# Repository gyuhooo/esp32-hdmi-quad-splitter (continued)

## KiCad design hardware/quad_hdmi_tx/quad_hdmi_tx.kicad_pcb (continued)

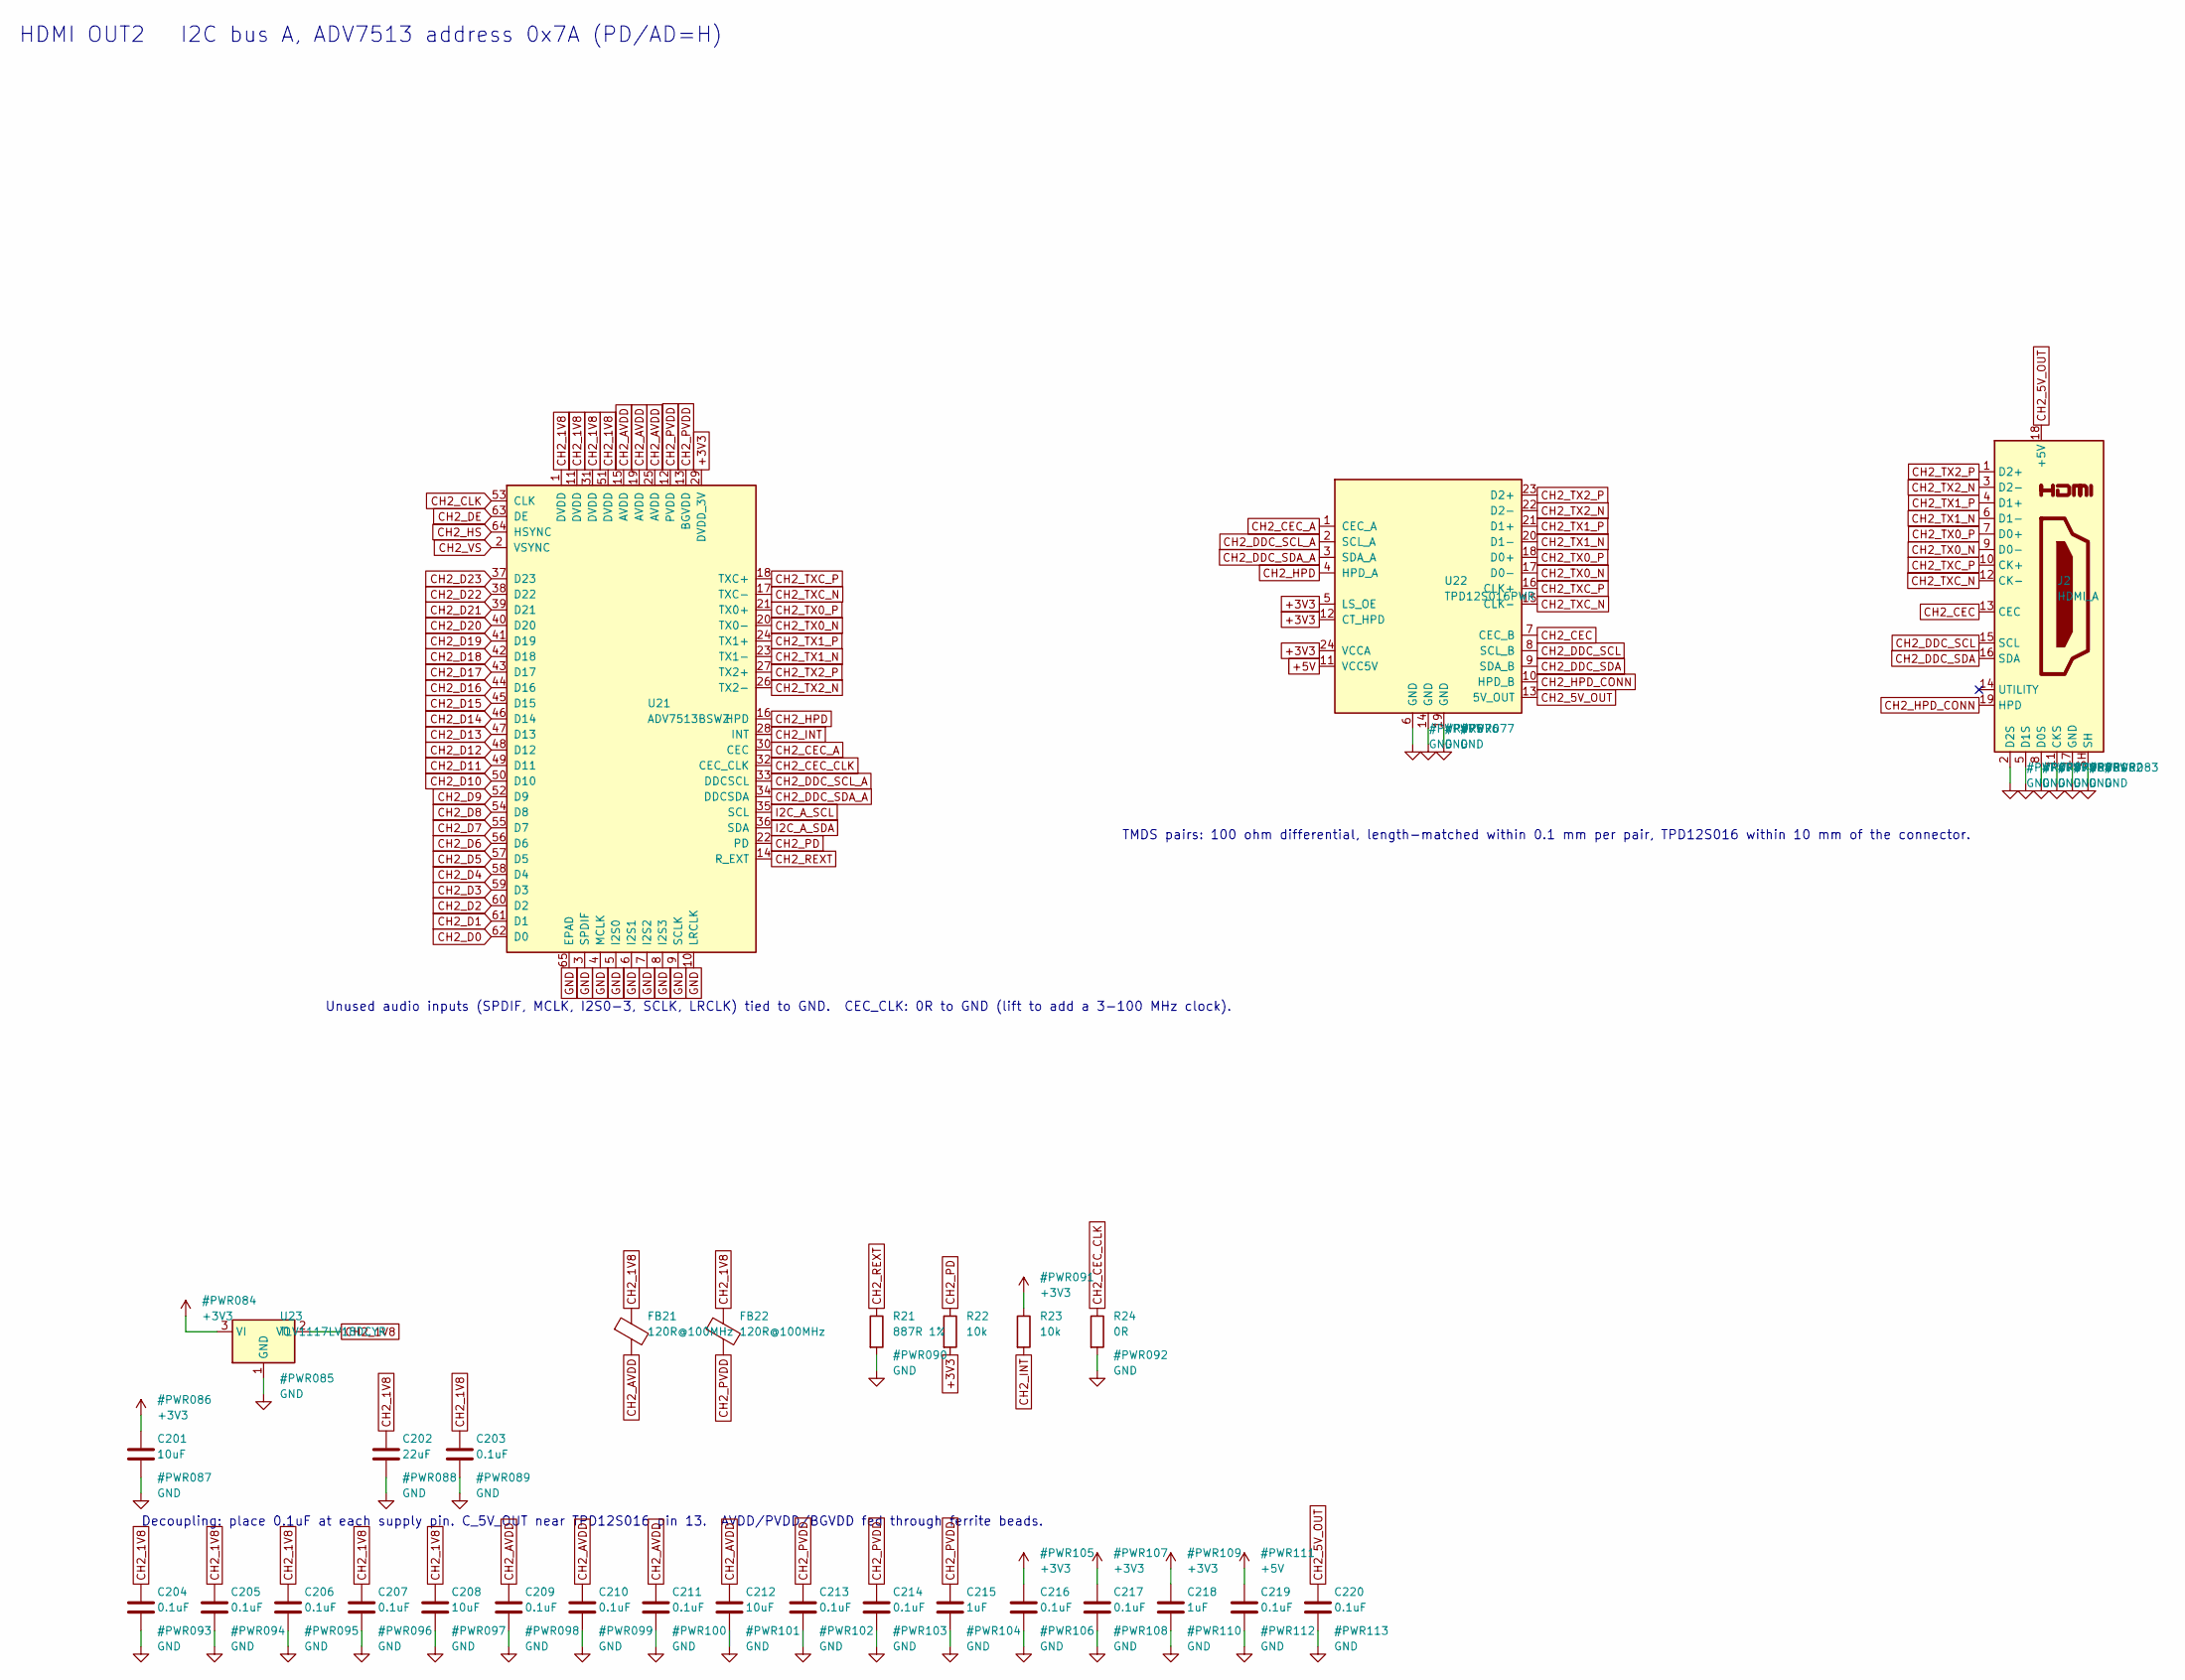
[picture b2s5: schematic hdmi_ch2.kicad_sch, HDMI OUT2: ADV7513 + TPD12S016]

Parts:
C201, C208, C212: 10uF; C_0603_1608Metric; MPN GRM188R60J106ME47D
C202: 22uF; C_0805_2012Metric; MPN GRM21BR60J226ME39L
C203, C204, C205, C206, C207, C209, C210, C211, C213, C214, C216, C217, C219, C220: 0.1uF; C_0402_1005Metric; MPN GRM155R71C104KA88D
C215, C218: 1uF; C_0603_1608Metric; MPN GRM188R61A105KA61D
FB21, FB22: 120R@100MHz; L_0603_1608Metric; MPN BLM18PG121SN1D
J2: HDMI_A; HDMI_A_Molex_208658-1001_Horizontal; MPN 208658-1001
R21: 887R 1%; R_0402_1005Metric; MPN RC0402FR-07887RL
R22, R23: 10k; R_0402_1005Metric; MPN RC0402FR-0710KL
R24: 0R; R_0402_1005Metric; MPN RC0402FR-070RL
U21: ADV7513BSWZ; LQFP-64-1EP_10x10mm_P0.5mm_EP5x5mm; MPN ADV7513BSWZ
U22: TPD12S016PWR; TSSOP-24_4.4x7.8mm_P0.65mm; MPN TPD12S016PWR
U23: TLV1117LV18DCYR; SOT-223-3_TabPin2; MPN TLV1117LV18DCYR

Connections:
+3V3: C201.1, C216.1, C217.1, C218.1, R22.2, R23.1, U21.29 (DVDD_3V), U22.5 (LS_OE), U22.12 (CT_HPD), U22.24 (VCCA), U23.3 (VI); also elsewhere on the board
+5V: C219.1, U22.11 (VCC5V); also elsewhere on the board
CH2_1V8: C202.1, C203.1, C204.1, C205.1, C206.1, C207.1, C208.1, FB21.1, FB22.1, U21.1 (DVDD), U21.11 (DVDD), U21.31 (DVDD), U21.51 (DVDD), U23.2 (VO)
CH2_5V_OUT: C220.1, J2.18 (+5V), U22.13 (5V_OUT)
CH2_AVDD: C209.1, C210.1, C211.1, C212.1, FB21.2, U21.15 (AVDD), U21.19 (AVDD), U21.25 (AVDD)
CH2_CEC: J2.13 (CEC), U22.7 (CEC_B)
CH2_CEC_A: U21.30 (CEC), U22.1 (CEC_A)
CH2_CEC_CLK: R24.1, U21.32 (CEC_CLK)
CH2_CLK: U21.53 (CLK); also elsewhere on the board
CH2_D0: U21.62 (D0); also elsewhere on the board
CH2_D1: U21.61 (D1); also elsewhere on the board
CH2_D2: U21.60 (D2); also elsewhere on the board
CH2_D3: U21.59 (D3); also elsewhere on the board
CH2_D4: U21.58 (D4); also elsewhere on the board
CH2_D5: U21.57 (D5); also elsewhere on the board
CH2_D6: U21.56 (D6); also elsewhere on the board
CH2_D7: U21.55 (D7); also elsewhere on the board
CH2_D8: U21.54 (D8); also elsewhere on the board
CH2_D9: U21.52 (D9); also elsewhere on the board
CH2_D10: U21.50 (D10); also elsewhere on the board
CH2_D11: U21.49 (D11); also elsewhere on the board
CH2_D12: U21.48 (D12); also elsewhere on the board
CH2_D13: U21.47 (D13); also elsewhere on the board
CH2_D14: U21.46 (D14); also elsewhere on the board
CH2_D15: U21.45 (D15); also elsewhere on the board
CH2_D16: U21.44 (D16); also elsewhere on the board
CH2_D17: U21.43 (D17); also elsewhere on the board
CH2_D18: U21.42 (D18); also elsewhere on the board
CH2_D19: U21.41 (D19); also elsewhere on the board
CH2_D20: U21.40 (D20); also elsewhere on the board
CH2_D21: U21.39 (D21); also elsewhere on the board
CH2_D22: U21.38 (D22); also elsewhere on the board
CH2_D23: U21.37 (D23); also elsewhere on the board
CH2_DDC_SCL: J2.15 (SCL), U22.8 (SCL_B)
CH2_DDC_SCL_A: U21.33 (DDCSCL), U22.2 (SCL_A)
CH2_DDC_SDA: J2.16 (SDA), U22.9 (SDA_B)
CH2_DDC_SDA_A: U21.34 (DDCSDA), U22.3 (SDA_A)
CH2_DE: U21.63 (DE); also elsewhere on the board
CH2_HPD: U21.16 (HPD), U22.4 (HPD_A); also elsewhere on the board
CH2_HPD_CONN: J2.19 (HPD), U22.10 (HPD_B)
CH2_HS: U21.64 (HSYNC); also elsewhere on the board
CH2_INT: R23.2, U21.28 (INT); also elsewhere on the board
CH2_PD: R22.1, U21.22 (PD)
CH2_PVDD: C213.1, C214.1, C215.1, FB22.2, U21.12 (PVDD), U21.13 (BGVDD)
CH2_REXT: R21.1, U21.14 (R_EXT)
CH2_TX0_N: J2.9 (D0-), U21.20 (TX0-), U22.17 (D0-)
CH2_TX0_P: J2.7 (D0+), U21.21 (TX0+), U22.18 (D0+)
CH2_TX1_N: J2.6 (D1-), U21.23 (TX1-), U22.20 (D1-)
CH2_TX1_P: J2.4 (D1+), U21.24 (TX1+), U22.21 (D1+)
CH2_TX2_N: J2.3 (D2-), U21.26 (TX2-), U22.22 (D2-)
CH2_TX2_P: J2.1 (D2+), U21.27 (TX2+), U22.23 (D2+)
CH2_TXC_N: J2.12 (CK-), U21.17 (TXC-), U22.15 (CLK-)
CH2_TXC_P: J2.10 (CK+), U21.18 (TXC+), U22.16 (CLK+)
CH2_VS: U21.2 (VSYNC); also elsewhere on the board
GND: C201.2, C202.2, C203.2, C204.2, C205.2, C206.2, C207.2, C208.2, C209.2, C210.2, C211.2, C212.2, C213.2, C214.2, C215.2, C216.2, C217.2, C218.2, C219.2, C220.2, J2.2 (D2S), J2.5 (D1S), J2.8 (D0S), J2.11 (CKS), J2.17 (GND), J2.SH, R21.2, R24.2, U21.3 (SPDIF), U21.4 (MCLK), U21.5 (I2S0), U21.6 (I2S1), U21.7 (I2S2), U21.8 (I2S3), U21.9 (SCLK), U21.10 (LRCLK), U21.65 (EPAD), U22.6 (GND), U22.14 (GND), U22.19 (GND), U23.1 (GND); also elsewhere on the board
I2C_A_SCL: U21.35 (SCL); also elsewhere on the board
I2C_A_SDA: U21.36 (SDA); also elsewhere on the board

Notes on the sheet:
HDMI OUT2 I2C bus A, ADV7513 address 0x7A (PD/AD=H)
Unused audio inputs (SPDIF, MCLK, I2S0-3, SCLK, LRCLK) tied to GND. CEC_CLK: 0R to GND (lift to add a 3-100 MHz clock).
Decoupling: place 0.1uF at each supply pin. C_5V_OUT near TPD12S016 pin 13. AVDD/PVDD/BGVDD fed through ferrite beads.
TMDS pairs: 100 ohm differential, length-matched within 0.1 mm per pair, TPD12S016 within 10 mm of the connector.

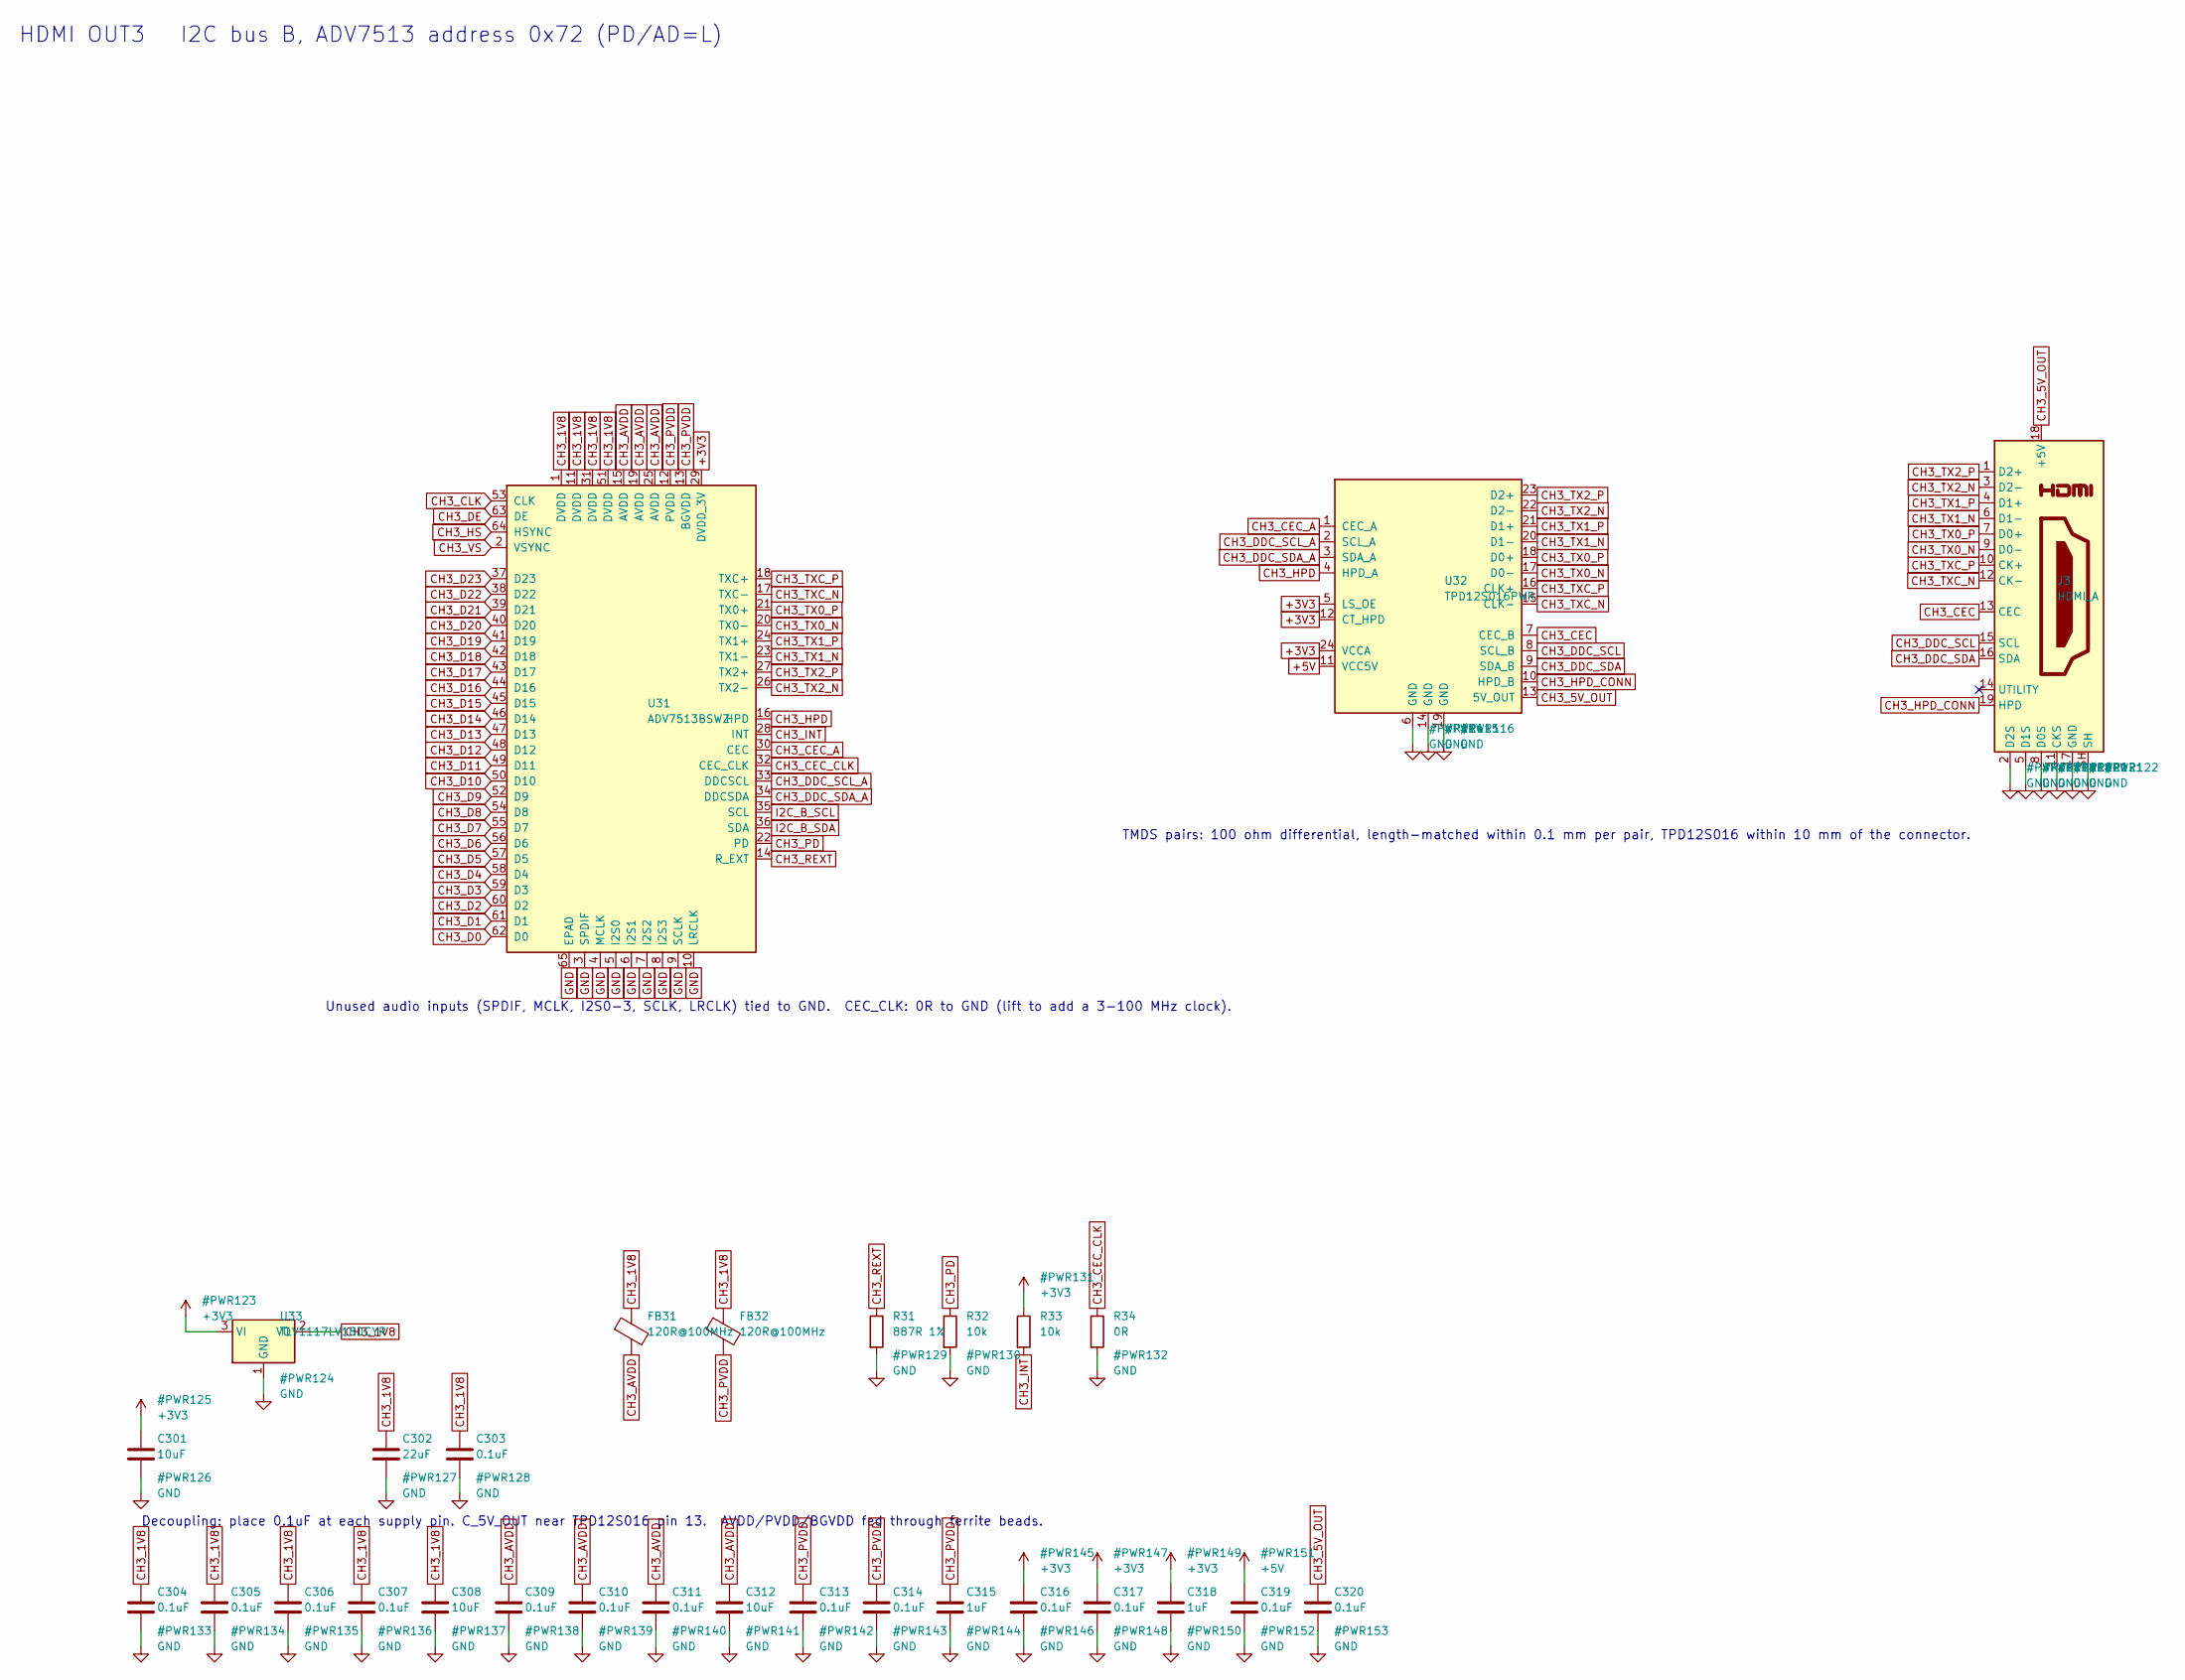
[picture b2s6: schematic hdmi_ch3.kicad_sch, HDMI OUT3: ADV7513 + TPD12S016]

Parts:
C301, C308, C312: 10uF; C_0603_1608Metric; MPN GRM188R60J106ME47D
C302: 22uF; C_0805_2012Metric; MPN GRM21BR60J226ME39L
C303, C304, C305, C306, C307, C309, C310, C311, C313, C314, C316, C317, C319, C320: 0.1uF; C_0402_1005Metric; MPN GRM155R71C104KA88D
C315, C318: 1uF; C_0603_1608Metric; MPN GRM188R61A105KA61D
FB31, FB32: 120R@100MHz; L_0603_1608Metric; MPN BLM18PG121SN1D
J3: HDMI_A; HDMI_A_Molex_208658-1001_Horizontal; MPN 208658-1001
R31: 887R 1%; R_0402_1005Metric; MPN RC0402FR-07887RL
R32, R33: 10k; R_0402_1005Metric; MPN RC0402FR-0710KL
R34: 0R; R_0402_1005Metric; MPN RC0402FR-070RL
U31: ADV7513BSWZ; LQFP-64-1EP_10x10mm_P0.5mm_EP5x5mm; MPN ADV7513BSWZ
U32: TPD12S016PWR; TSSOP-24_4.4x7.8mm_P0.65mm; MPN TPD12S016PWR
U33: TLV1117LV18DCYR; SOT-223-3_TabPin2; MPN TLV1117LV18DCYR

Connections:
+3V3: C301.1, C316.1, C317.1, C318.1, R33.1, U31.29 (DVDD_3V), U32.5 (LS_OE), U32.12 (CT_HPD), U32.24 (VCCA), U33.3 (VI); also elsewhere on the board
+5V: C319.1, U32.11 (VCC5V); also elsewhere on the board
CH3_1V8: C302.1, C303.1, C304.1, C305.1, C306.1, C307.1, C308.1, FB31.1, FB32.1, U31.1 (DVDD), U31.11 (DVDD), U31.31 (DVDD), U31.51 (DVDD), U33.2 (VO)
CH3_5V_OUT: C320.1, J3.18 (+5V), U32.13 (5V_OUT)
CH3_AVDD: C309.1, C310.1, C311.1, C312.1, FB31.2, U31.15 (AVDD), U31.19 (AVDD), U31.25 (AVDD)
CH3_CEC: J3.13 (CEC), U32.7 (CEC_B)
CH3_CEC_A: U31.30 (CEC), U32.1 (CEC_A)
CH3_CEC_CLK: R34.1, U31.32 (CEC_CLK)
CH3_CLK: U31.53 (CLK); also elsewhere on the board
CH3_D0: U31.62 (D0); also elsewhere on the board
CH3_D1: U31.61 (D1); also elsewhere on the board
CH3_D2: U31.60 (D2); also elsewhere on the board
CH3_D3: U31.59 (D3); also elsewhere on the board
CH3_D4: U31.58 (D4); also elsewhere on the board
CH3_D5: U31.57 (D5); also elsewhere on the board
CH3_D6: U31.56 (D6); also elsewhere on the board
CH3_D7: U31.55 (D7); also elsewhere on the board
CH3_D8: U31.54 (D8); also elsewhere on the board
CH3_D9: U31.52 (D9); also elsewhere on the board
CH3_D10: U31.50 (D10); also elsewhere on the board
CH3_D11: U31.49 (D11); also elsewhere on the board
CH3_D12: U31.48 (D12); also elsewhere on the board
CH3_D13: U31.47 (D13); also elsewhere on the board
CH3_D14: U31.46 (D14); also elsewhere on the board
CH3_D15: U31.45 (D15); also elsewhere on the board
CH3_D16: U31.44 (D16); also elsewhere on the board
CH3_D17: U31.43 (D17); also elsewhere on the board
CH3_D18: U31.42 (D18); also elsewhere on the board
CH3_D19: U31.41 (D19); also elsewhere on the board
CH3_D20: U31.40 (D20); also elsewhere on the board
CH3_D21: U31.39 (D21); also elsewhere on the board
CH3_D22: U31.38 (D22); also elsewhere on the board
CH3_D23: U31.37 (D23); also elsewhere on the board
CH3_DDC_SCL: J3.15 (SCL), U32.8 (SCL_B)
CH3_DDC_SCL_A: U31.33 (DDCSCL), U32.2 (SCL_A)
CH3_DDC_SDA: J3.16 (SDA), U32.9 (SDA_B)
CH3_DDC_SDA_A: U31.34 (DDCSDA), U32.3 (SDA_A)
CH3_DE: U31.63 (DE); also elsewhere on the board
CH3_HPD: U31.16 (HPD), U32.4 (HPD_A); also elsewhere on the board
CH3_HPD_CONN: J3.19 (HPD), U32.10 (HPD_B)
CH3_HS: U31.64 (HSYNC); also elsewhere on the board
CH3_INT: R33.2, U31.28 (INT); also elsewhere on the board
CH3_PD: R32.1, U31.22 (PD)
CH3_PVDD: C313.1, C314.1, C315.1, FB32.2, U31.12 (PVDD), U31.13 (BGVDD)
CH3_REXT: R31.1, U31.14 (R_EXT)
CH3_TX0_N: J3.9 (D0-), U31.20 (TX0-), U32.17 (D0-)
CH3_TX0_P: J3.7 (D0+), U31.21 (TX0+), U32.18 (D0+)
CH3_TX1_N: J3.6 (D1-), U31.23 (TX1-), U32.20 (D1-)
CH3_TX1_P: J3.4 (D1+), U31.24 (TX1+), U32.21 (D1+)
CH3_TX2_N: J3.3 (D2-), U31.26 (TX2-), U32.22 (D2-)
CH3_TX2_P: J3.1 (D2+), U31.27 (TX2+), U32.23 (D2+)
CH3_TXC_N: J3.12 (CK-), U31.17 (TXC-), U32.15 (CLK-)
CH3_TXC_P: J3.10 (CK+), U31.18 (TXC+), U32.16 (CLK+)
CH3_VS: U31.2 (VSYNC); also elsewhere on the board
GND: C301.2, C302.2, C303.2, C304.2, C305.2, C306.2, C307.2, C308.2, C309.2, C310.2, C311.2, C312.2, C313.2, C314.2, C315.2, C316.2, C317.2, C318.2, C319.2, C320.2, J3.2 (D2S), J3.5 (D1S), J3.8 (D0S), J3.11 (CKS), J3.17 (GND), J3.SH, R31.2, R32.2, R34.2, U31.3 (SPDIF), U31.4 (MCLK), U31.5 (I2S0), U31.6 (I2S1), U31.7 (I2S2), U31.8 (I2S3), U31.9 (SCLK), U31.10 (LRCLK), U31.65 (EPAD), U32.6 (GND), U32.14 (GND), U32.19 (GND), U33.1 (GND); also elsewhere on the board
I2C_B_SCL: U31.35 (SCL); also elsewhere on the board
I2C_B_SDA: U31.36 (SDA); also elsewhere on the board

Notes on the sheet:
HDMI OUT3 I2C bus B, ADV7513 address 0x72 (PD/AD=L)
Unused audio inputs (SPDIF, MCLK, I2S0-3, SCLK, LRCLK) tied to GND. CEC_CLK: 0R to GND (lift to add a 3-100 MHz clock).
Decoupling: place 0.1uF at each supply pin. C_5V_OUT near TPD12S016 pin 13. AVDD/PVDD/BGVDD fed through ferrite beads.
TMDS pairs: 100 ohm differential, length-matched within 0.1 mm per pair, TPD12S016 within 10 mm of the connector.

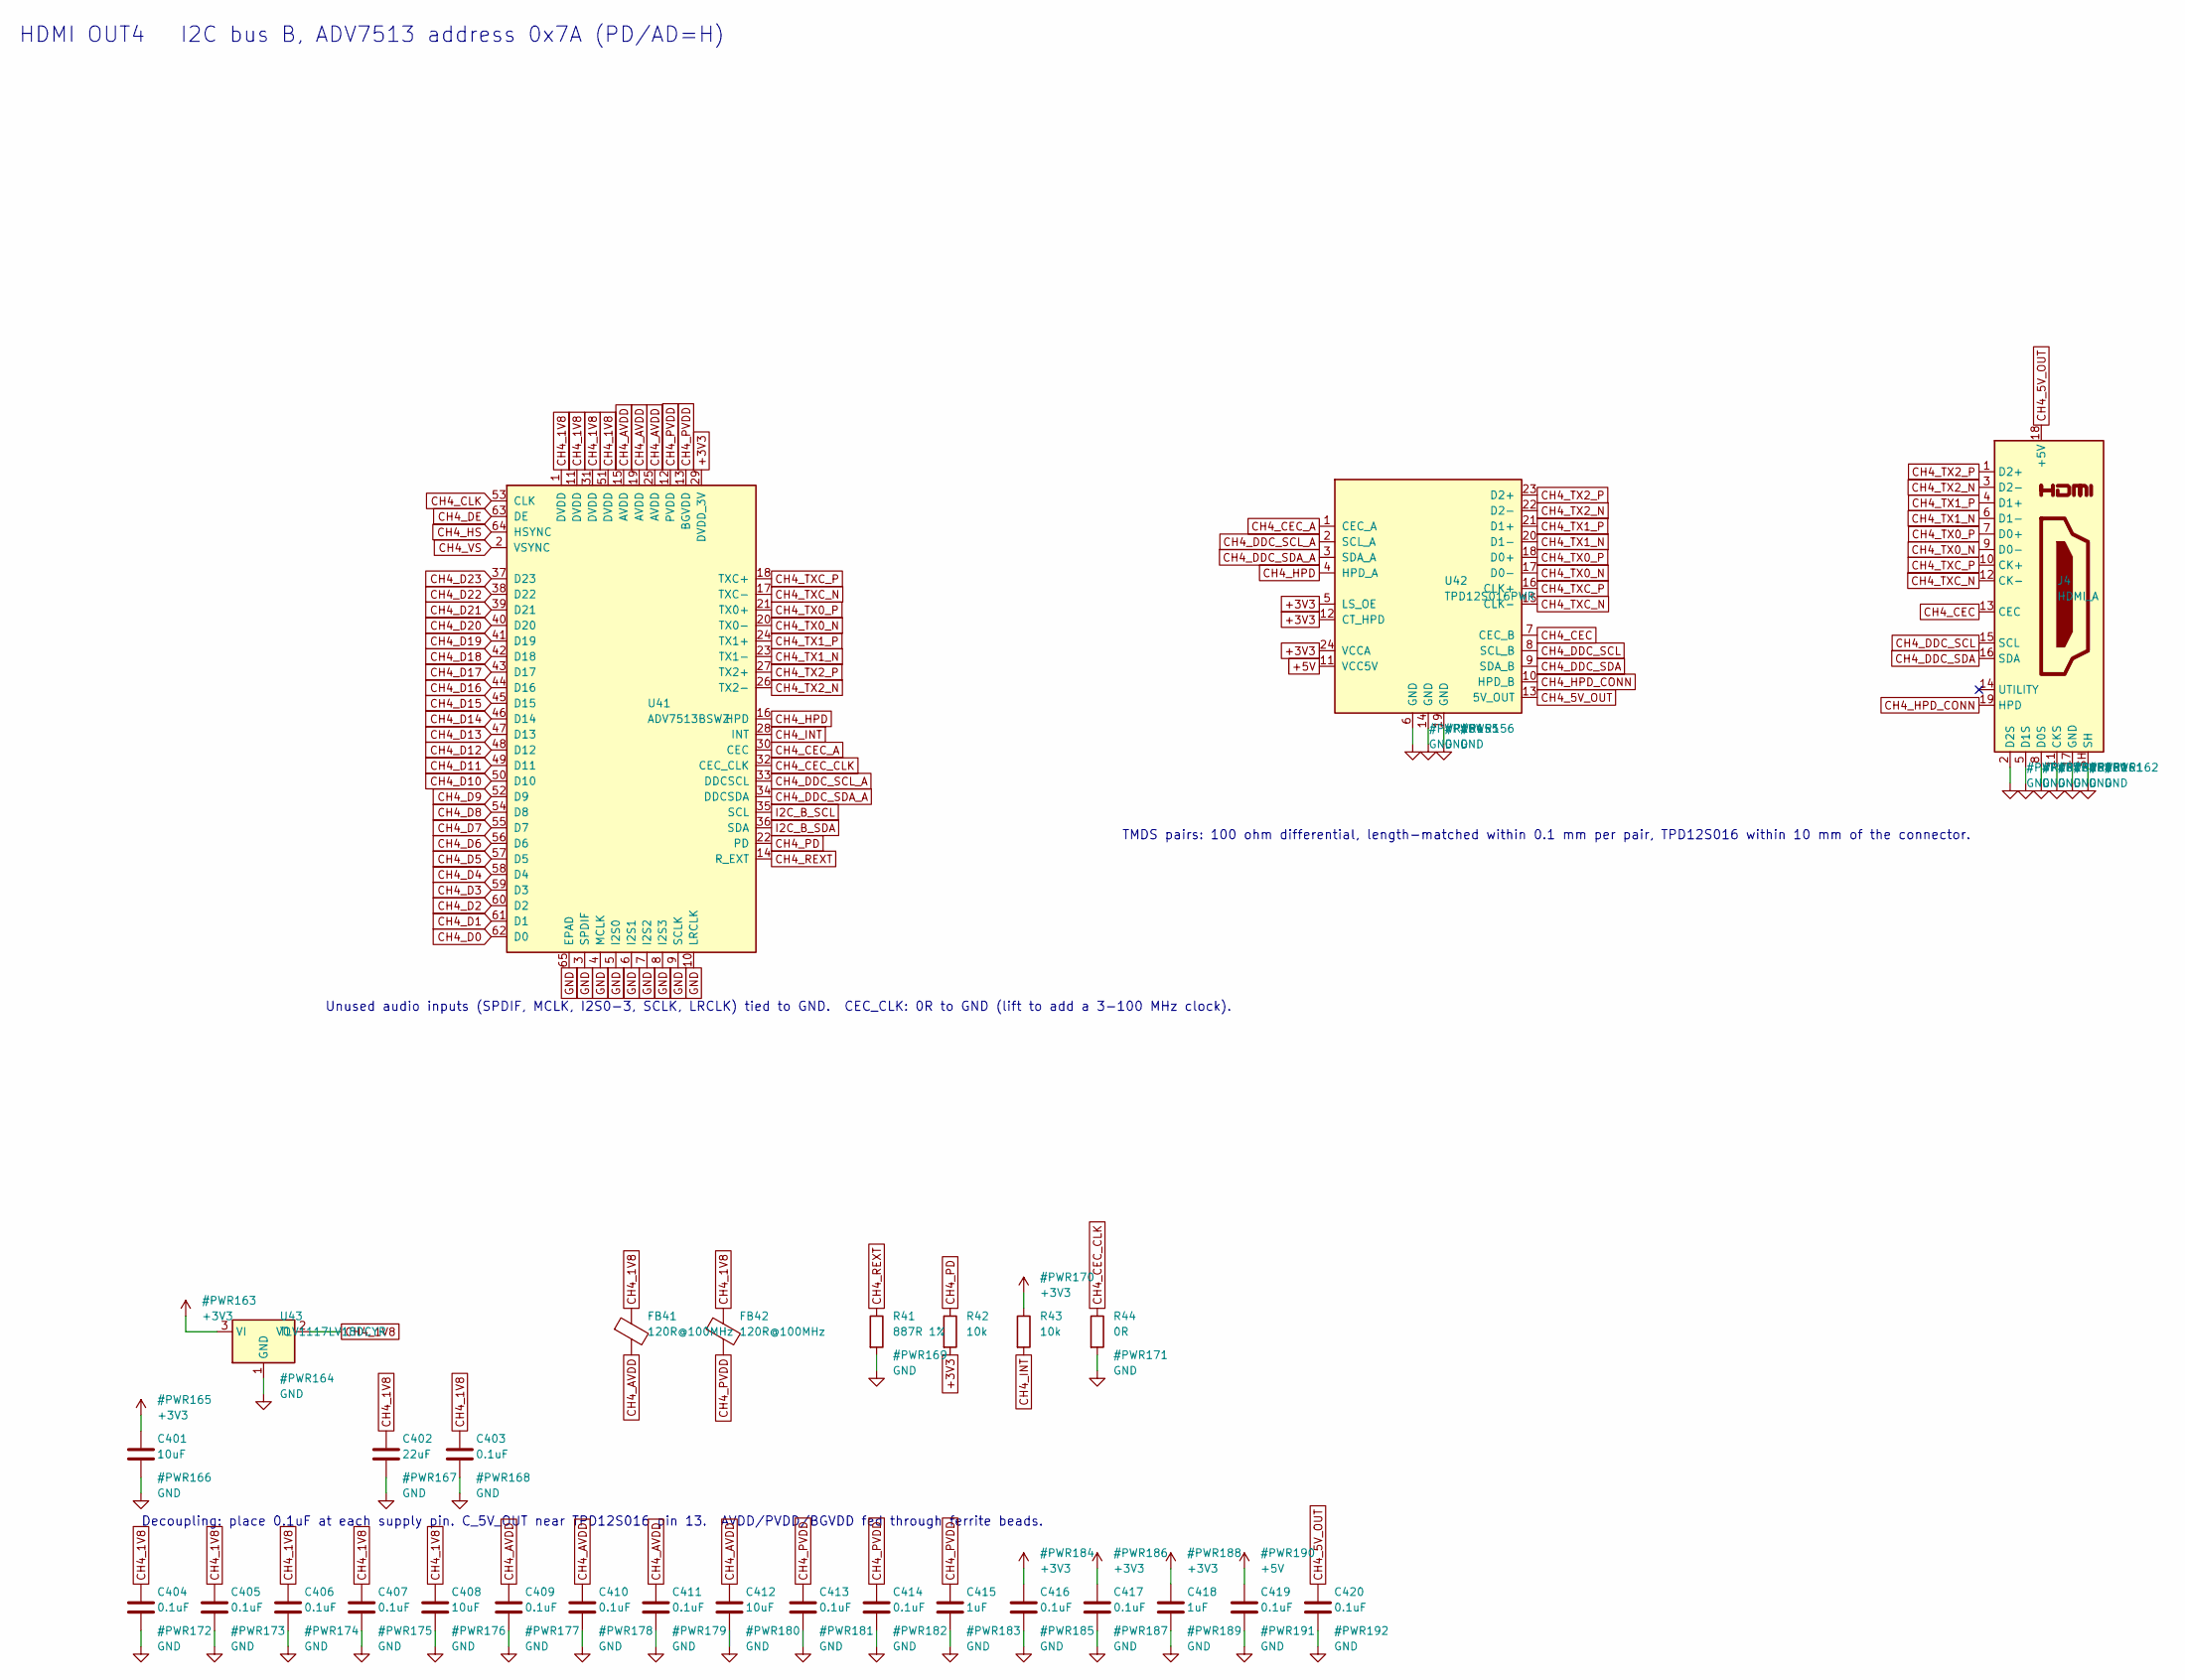
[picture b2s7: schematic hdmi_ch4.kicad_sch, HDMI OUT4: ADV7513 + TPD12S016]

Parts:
C401, C408, C412: 10uF; C_0603_1608Metric; MPN GRM188R60J106ME47D
C402: 22uF; C_0805_2012Metric; MPN GRM21BR60J226ME39L
C403, C404, C405, C406, C407, C409, C410, C411, C413, C414, C416, C417, C419, C420: 0.1uF; C_0402_1005Metric; MPN GRM155R71C104KA88D
C415, C418: 1uF; C_0603_1608Metric; MPN GRM188R61A105KA61D
FB41, FB42: 120R@100MHz; L_0603_1608Metric; MPN BLM18PG121SN1D
J4: HDMI_A; HDMI_A_Molex_208658-1001_Horizontal; MPN 208658-1001
R41: 887R 1%; R_0402_1005Metric; MPN RC0402FR-07887RL
R42, R43: 10k; R_0402_1005Metric; MPN RC0402FR-0710KL
R44: 0R; R_0402_1005Metric; MPN RC0402FR-070RL
U41: ADV7513BSWZ; LQFP-64-1EP_10x10mm_P0.5mm_EP5x5mm; MPN ADV7513BSWZ
U42: TPD12S016PWR; TSSOP-24_4.4x7.8mm_P0.65mm; MPN TPD12S016PWR
U43: TLV1117LV18DCYR; SOT-223-3_TabPin2; MPN TLV1117LV18DCYR

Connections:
+3V3: C401.1, C416.1, C417.1, C418.1, R42.2, R43.1, U41.29 (DVDD_3V), U42.5 (LS_OE), U42.12 (CT_HPD), U42.24 (VCCA), U43.3 (VI); also elsewhere on the board
+5V: C419.1, U42.11 (VCC5V); also elsewhere on the board
CH4_1V8: C402.1, C403.1, C404.1, C405.1, C406.1, C407.1, C408.1, FB41.1, FB42.1, U41.1 (DVDD), U41.11 (DVDD), U41.31 (DVDD), U41.51 (DVDD), U43.2 (VO)
CH4_5V_OUT: C420.1, J4.18 (+5V), U42.13 (5V_OUT)
CH4_AVDD: C409.1, C410.1, C411.1, C412.1, FB41.2, U41.15 (AVDD), U41.19 (AVDD), U41.25 (AVDD)
CH4_CEC: J4.13 (CEC), U42.7 (CEC_B)
CH4_CEC_A: U41.30 (CEC), U42.1 (CEC_A)
CH4_CEC_CLK: R44.1, U41.32 (CEC_CLK)
CH4_CLK: U41.53 (CLK); also elsewhere on the board
CH4_D0: U41.62 (D0); also elsewhere on the board
CH4_D1: U41.61 (D1); also elsewhere on the board
CH4_D2: U41.60 (D2); also elsewhere on the board
CH4_D3: U41.59 (D3); also elsewhere on the board
CH4_D4: U41.58 (D4); also elsewhere on the board
CH4_D5: U41.57 (D5); also elsewhere on the board
CH4_D6: U41.56 (D6); also elsewhere on the board
CH4_D7: U41.55 (D7); also elsewhere on the board
CH4_D8: U41.54 (D8); also elsewhere on the board
CH4_D9: U41.52 (D9); also elsewhere on the board
CH4_D10: U41.50 (D10); also elsewhere on the board
CH4_D11: U41.49 (D11); also elsewhere on the board
CH4_D12: U41.48 (D12); also elsewhere on the board
CH4_D13: U41.47 (D13); also elsewhere on the board
CH4_D14: U41.46 (D14); also elsewhere on the board
CH4_D15: U41.45 (D15); also elsewhere on the board
CH4_D16: U41.44 (D16); also elsewhere on the board
CH4_D17: U41.43 (D17); also elsewhere on the board
CH4_D18: U41.42 (D18); also elsewhere on the board
CH4_D19: U41.41 (D19); also elsewhere on the board
CH4_D20: U41.40 (D20); also elsewhere on the board
CH4_D21: U41.39 (D21); also elsewhere on the board
CH4_D22: U41.38 (D22); also elsewhere on the board
CH4_D23: U41.37 (D23); also elsewhere on the board
CH4_DDC_SCL: J4.15 (SCL), U42.8 (SCL_B)
CH4_DDC_SCL_A: U41.33 (DDCSCL), U42.2 (SCL_A)
CH4_DDC_SDA: J4.16 (SDA), U42.9 (SDA_B)
CH4_DDC_SDA_A: U41.34 (DDCSDA), U42.3 (SDA_A)
CH4_DE: U41.63 (DE); also elsewhere on the board
CH4_HPD: U41.16 (HPD), U42.4 (HPD_A); also elsewhere on the board
CH4_HPD_CONN: J4.19 (HPD), U42.10 (HPD_B)
CH4_HS: U41.64 (HSYNC); also elsewhere on the board
CH4_INT: R43.2, U41.28 (INT); also elsewhere on the board
CH4_PD: R42.1, U41.22 (PD)
CH4_PVDD: C413.1, C414.1, C415.1, FB42.2, U41.12 (PVDD), U41.13 (BGVDD)
CH4_REXT: R41.1, U41.14 (R_EXT)
CH4_TX0_N: J4.9 (D0-), U41.20 (TX0-), U42.17 (D0-)
CH4_TX0_P: J4.7 (D0+), U41.21 (TX0+), U42.18 (D0+)
CH4_TX1_N: J4.6 (D1-), U41.23 (TX1-), U42.20 (D1-)
CH4_TX1_P: J4.4 (D1+), U41.24 (TX1+), U42.21 (D1+)
CH4_TX2_N: J4.3 (D2-), U41.26 (TX2-), U42.22 (D2-)
CH4_TX2_P: J4.1 (D2+), U41.27 (TX2+), U42.23 (D2+)
CH4_TXC_N: J4.12 (CK-), U41.17 (TXC-), U42.15 (CLK-)
CH4_TXC_P: J4.10 (CK+), U41.18 (TXC+), U42.16 (CLK+)
CH4_VS: U41.2 (VSYNC); also elsewhere on the board
GND: C401.2, C402.2, C403.2, C404.2, C405.2, C406.2, C407.2, C408.2, C409.2, C410.2, C411.2, C412.2, C413.2, C414.2, C415.2, C416.2, C417.2, C418.2, C419.2, C420.2, J4.2 (D2S), J4.5 (D1S), J4.8 (D0S), J4.11 (CKS), J4.17 (GND), J4.SH, R41.2, R44.2, U41.3 (SPDIF), U41.4 (MCLK), U41.5 (I2S0), U41.6 (I2S1), U41.7 (I2S2), U41.8 (I2S3), U41.9 (SCLK), U41.10 (LRCLK), U41.65 (EPAD), U42.6 (GND), U42.14 (GND), U42.19 (GND), U43.1 (GND); also elsewhere on the board
I2C_B_SCL: U41.35 (SCL); also elsewhere on the board
I2C_B_SDA: U41.36 (SDA); also elsewhere on the board

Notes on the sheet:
HDMI OUT4 I2C bus B, ADV7513 address 0x7A (PD/AD=H)
Unused audio inputs (SPDIF, MCLK, I2S0-3, SCLK, LRCLK) tied to GND. CEC_CLK: 0R to GND (lift to add a 3-100 MHz clock).
Decoupling: place 0.1uF at each supply pin. C_5V_OUT near TPD12S016 pin 13. AVDD/PVDD/BGVDD fed through ferrite beads.
TMDS pairs: 100 ohm differential, length-matched within 0.1 mm per pair, TPD12S016 within 10 mm of the connector.
